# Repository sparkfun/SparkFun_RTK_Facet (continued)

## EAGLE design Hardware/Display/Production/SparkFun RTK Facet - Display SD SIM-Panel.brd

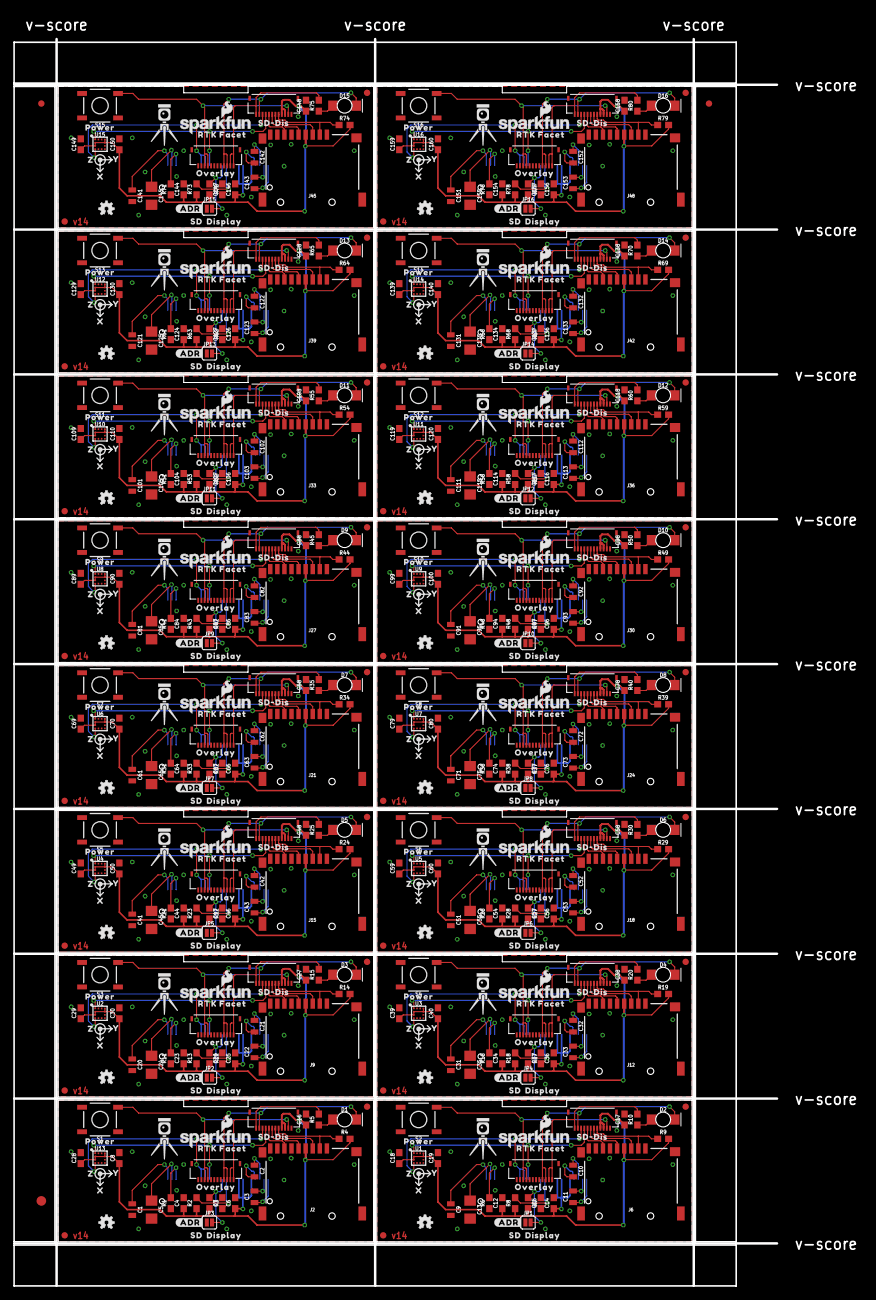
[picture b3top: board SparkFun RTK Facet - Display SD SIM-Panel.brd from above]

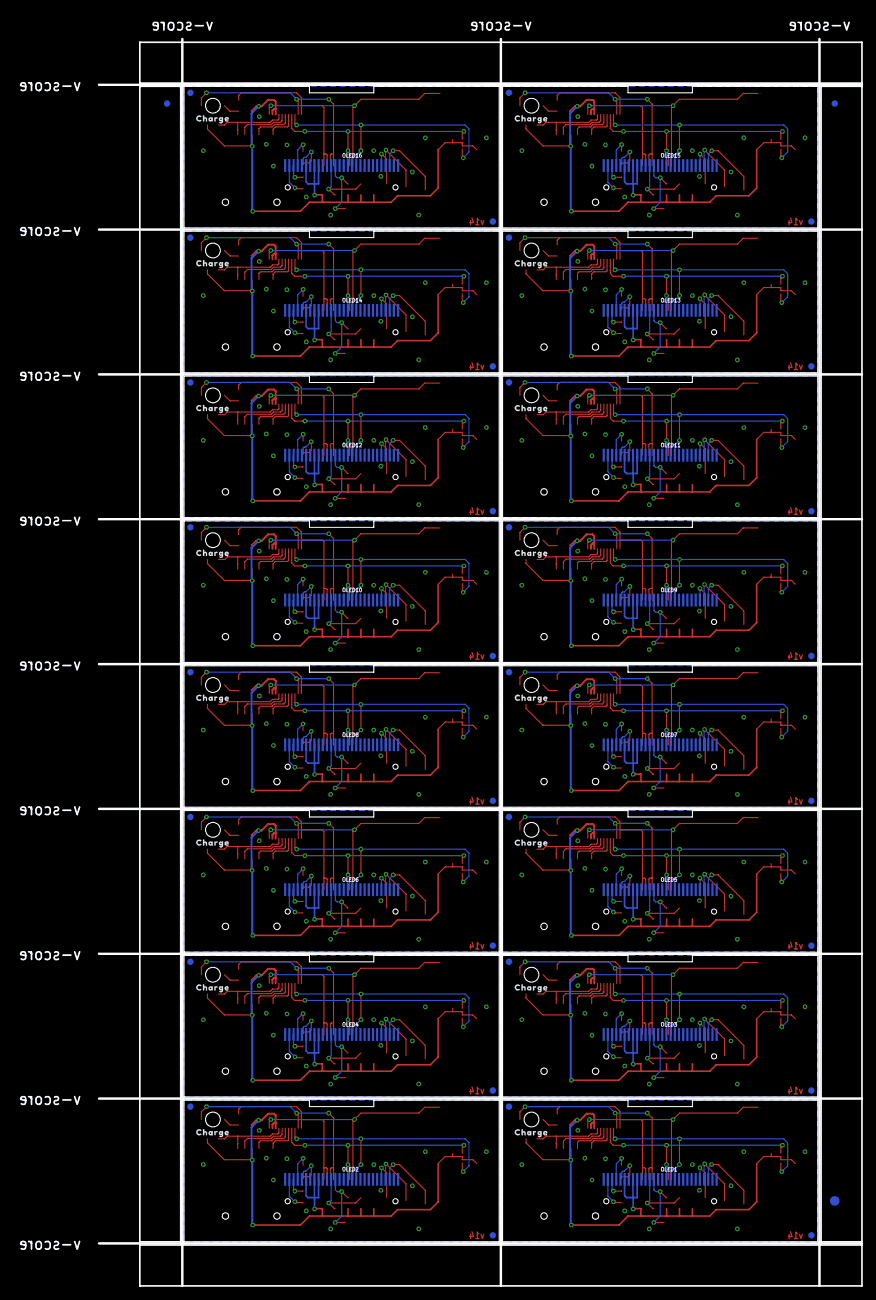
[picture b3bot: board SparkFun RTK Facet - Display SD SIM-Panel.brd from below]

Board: 2 copper layers, 118.6 x 193.8 mm, 662 parts (67 on the bottom side), 336 nets.

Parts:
C1, C9, C20, C31, C41, C51, C61, C71, C81, C91, C101, C111, C121, C131, C141, C151: 2.2uF; 0805
C2, C3, C10, C11, C21, C22, C32, C33, C42, C43, C52, C53, C62, C63, C72, C73, C82, C83, C92, C93, C102, C103, C112, C113, C122, C123, C132, C133, C142, C143, C152, C153: 1.0uF; 0805
C4, C6, C7, C12, C14, C15, C23, C25, C26, C34, C36, C37, C44, C46, C47, C54, C56, C57, C64, C66, C67, C74, C76, C77, C84, C86, C87, C94, C96, C97, C104, C106, C107, C114, C116, C117, C124, C126, C127, C134, C136, C137, C144, C146, C147, C154, C156, C157: 1.0uF; 0603
C5, C13, C24, C35, C45, C55, C65, C75, C85, C95, C105, C115, C125, C135, C145, C155: 4.7uF; 1206
C8, C19, C30, C40, C50, C60, C70, C80, C90, C100, C110, C120, C130, C140, C150, C160: 10uF; 0603
C16, C17, C18, C27, C28, C29, C38, C39, C48, C49, C58, C59, C68, C69, C78, C79, C88, C89, C98, C99, C108, C109, C118, C119, C128, C129, C138, C139, C148, C149, C158, C159: 0.1uF; 0603
D1, D2, D3, D4, D5, D6, D7, D8, D9, D10, D11, D12, D13, D14, D15, D16: Green; LED-1206-BOTTOM
E$1, E$2, E$3, E$4: FIDUCIAL-1X2
E$5, E$6: FIDUCIAL-1.5X3
FID1, FID2, FID3, FID4, FID5, FID6, FID7, FID8, FID9, FID10, FID11, FID12, FID13, FID14, FID15, FID16, FID17, FID18, FID19, FID20, FID21, FID22, FID23, FID24, FID25, FID26, FID27, FID28, FID29, FID30, FID31, FID32, FID33, FID34, FID35, FID36, FID37, FID38, FID39, FID40, FID41, FID42, FID43, FID44, FID45, FID46, FID47, FID48, FID49, FID50, FID51, FID52, FID53, FID54, FID55, FID56, FID57, FID58, FID59, FID60, FID61, FID62, FID63, FID64: FIDUCIAL1X2; FIDUCIAL-1X2
J1, J3, J4, J5, J7, J8, J10, J11, J13, J14, J16, J17, J19, J20, J22, J23, J25, J26, J28, J29, J31, J32, J34, J35, J37, J38, J40, J41, J43, J44, J46, J47: FPC_12_0.5MM_BACKFLIP; FPC_12_DOUBLESIDED_BACKFLIP
J2, J6, J9, J12, J15, J18, J21, J24, J27, J30, J33, J36, J39, J42, J45, J48: MICRO-SD-PUSH-PUSH-EXT-PIN; MICROSD-EXTERNALPIN
JP1, JP2, JP3, JP4, JP5, JP6, JP7, JP8, JP9, JP10, JP11, JP12, JP13, JP14, JP15, JP16: SMT-JUMPER_2_NO_SILK
LOGO1, LOGO3, LOGO4, LOGO7, LOGO9, LOGO11, LOGO13, LOGO15, LOGO17, LOGO19, LOGO21, LOGO23, LOGO25, LOGO27, LOGO29, LOGO31: OSHW-LOGOMINI; OSHW-LOGO-MINI
LOGO2, LOGO5, LOGO6, LOGO8, LOGO10, LOGO12, LOGO14, LOGO16, LOGO18, LOGO20, LOGO22, LOGO24, LOGO26, LOGO28, LOGO30, LOGO32: SFE_LOGO_NAME_FLAME.1_INCH; SFE_LOGO_NAME_FLAME_.1
OLED1, OLED2, OLED3, OLED4, OLED5, OLED6, OLED7, OLED8, OLED9, OLED10, OLED11, OLED12, OLED13, OLED14, OLED15, OLED16: OLED0.66; OLED-0.66-64X48
R1, R6, R11, R16, R21, R26, R31, R36, R41, R46, R51, R56, R61, R66, R71, R76: 390k; 0603
R2, R3, R7, R8, R12, R13, R17, R18, R22, R23, R27, R28, R32, R33, R37, R38, R42, R43, R47, R48, R52, R53, R57, R58, R62, R63, R67, R68, R72, R73, R77, R78: 10k; 0603
R4, R9, R14, R19, R24, R29, R34, R39, R44, R49, R54, R59, R64, R69, R74, R79: 100k; 0603
R5, R10, R15, R20, R25, R30, R35, R40, R45, R50, R55, R60, R65, R70, R75, R80: 1k; 0603
S1, S2, S3, S4, S5, S6, S7, S8, S9, S10, S11, S12, S13, S14, S15, S16: MOMENTARY-SWITCH-SPST-SMD-5.2MM-TALL; TACTILE_SWITCH_SMD_5.2MM
U1, U2, U3, U4, U5, U6, U7, U8, U9, U10, U11, U12, U13, U14, U15, U16: LIS2DH12; LGA-12-LISDH12
U$1, U$16, U$28, U$40, U$52, U$64, U$76, U$88, U$100, U$112, U$124, U$136, U$148, U$160, U$172, U$184: SD#DIS0
U$2, U$18, U$30, U$42, U$54, U$66, U$78, U$90, U$102, U$114, U$126, U$138, U$150, U$162, U$174, U$186: OVERLAY0
U$3, U$6, U$25, U$37, U$49, U$61, U$73, U$85, U$97, U$109, U$121, U$133, U$145, U$157, U$169, U$181: DISPLAY0
U$4, U$14, U$26, U$38, U$50, U$62, U$74, U$86, U$98, U$110, U$122, U$134, U$146, U$158, U$170, U$182: SD1
U$5, U$24, U$36, U$48, U$60, U$72, U$84, U$96, U$108, U$120, U$132, U$144, U$156, U$168, U$180, U$192: RTK5#SVG0
U$7, U$15, U$27, U$39, U$51, U$63, U$75, U$87, U$99, U$111, U$123, U$135, U$147, U$159, U$171, U$183: #ADR#0
U$8, U$17, U$29, U$41, U$53, U$65, U$77, U$89, U$101, U$113, U$125, U$137, U$149, U$161, U$173, U$185: CHARGE0
U$9, U$19, U$31, U$43, U$55, U$67, U$79, U$91, U$103, U$115, U$127, U$139, U$151, U$163, U$175, U$187: POWER0
U$10, U$20, U$32, U$44, U$56, U$68, U$80, U$92, U$104, U$116, U$128, U$140, U$152, U$164, U$176, U$188: X0
U$11, U$21, U$33, U$45, U$57, U$69, U$81, U$93, U$105, U$117, U$129, U$141, U$153, U$165, U$177, U$189: Y1
U$12, U$22, U$34, U$46, U$58, U$70, U$82, U$94, U$106, U$118, U$130, U$142, U$154, U$166, U$178, U$190: Z2
U$13, U$23, U$35, U$47, U$59, U$71, U$83, U$95, U$107, U$119, U$131, U$143, U$155, U$167, U$179, U$191: RTK_FACET0

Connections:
3.3V: C4.1, C6.1, C8.1, C16.1, C28.1, J1.3, J1.4, J2.4, OLED1.6, OLED1.8, OLED1.9, R2.1, R3.2, R4.2, U13.2, U13.3, U13.9, U13.10
3.3V1: C12.1, C14.1, C17.1, C18.1, C19.1, J4.3, J4.4, J6.4, OLED2.6, OLED2.8, OLED2.9, R7.2, R8.1, R9.2, U1.2, U1.3, U1.9, U1.10
3.3V2: C23.1, C25.1, C27.1, C29.1, C30.1, J7.3, J7.4, J9.4, OLED3.6, OLED3.8, OLED3.9, R12.2, R13.1, R14.2, U2.2, U2.3, U2.9, U2.10
3.3V3: C34.1, C36.1, C38.1, C39.1, C40.1, J10.3, J10.4, J12.4, OLED4.6, OLED4.8, OLED4.9, R17.2, R18.1, R19.2, U3.2, U3.3, U3.9, U3.10
3.3V4: C44.1, C46.1, C48.1, C49.1, C50.1, J13.3, J13.4, J15.4, OLED5.6, OLED5.8, OLED5.9, R22.2, R23.1, R24.2, U4.2, U4.3, U4.9, U4.10
3.3V5: C54.1, C56.1, C58.1, C59.1, C60.1, J16.3, J16.4, J18.4, OLED6.6, OLED6.8, OLED6.9, R27.2, R28.1, R29.2, U5.2, U5.3, U5.9, U5.10
3.3V6: C64.1, C66.1, C68.1, C69.1, C70.1, J19.3, J19.4, J21.4, OLED7.6, OLED7.8, OLED7.9, R32.2, R33.1, R34.2, U6.2, U6.3, U6.9, U6.10
3.3V7: C74.1, C76.1, C78.1, C79.1, C80.1, J22.3, J22.4, J24.4, OLED8.6, OLED8.8, OLED8.9, R37.2, R38.1, R39.2, U7.2, U7.3, U7.9, U7.10
3.3V8: C84.1, C86.1, C88.1, C89.1, C90.1, J25.3, J25.4, J27.4, OLED9.6, OLED9.8, OLED9.9, R42.2, R43.1, R44.2, U8.2, U8.3, U8.9, U8.10
3.3V9: C94.1, C96.1, C98.1, C99.1, C100.1, J28.3, J28.4, J30.4, OLED10.6, OLED10.8, OLED10.9, R47.2, R48.1, R49.2, U9.2, U9.3, U9.9, U9.10
3.3V10: C104.1, C106.1, C108.1, C109.1, C110.1, J31.3, J31.4, J33.4, OLED11.6, OLED11.8, OLED11.9, R52.2, R53.1, R54.2, U10.2, U10.3, U10.9, U10.10
3.3V11: C114.1, C116.1, C118.1, C119.1, C120.1, J34.3, J34.4, J36.4, OLED12.6, OLED12.8, OLED12.9, R57.2, R58.1, R59.2, U11.2, U11.3, U11.9, U11.10
3.3V12: C124.1, C126.1, C128.1, C129.1, C130.1, J37.3, J37.4, J39.4, OLED13.6, OLED13.8, OLED13.9, R62.2, R63.1, R64.2, U12.2, U12.3, U12.9, U12.10
3.3V13: C134.1, C136.1, C138.1, C139.1, C140.1, J40.3, J40.4, J42.4, OLED14.6, OLED14.8, OLED14.9, R67.2, R68.1, R69.2, U14.2, U14.3, U14.9, U14.10
3.3V14: C144.1, C146.1, C148.1, C149.1, C150.1, J43.3, J43.4, J45.4, OLED15.6, OLED15.8, OLED15.9, R72.2, R73.1, R74.2, U15.2, U15.3, U15.9, U15.10
3.3V15: C154.1, C156.1, C158.1, C159.1, C160.1, J46.3, J46.4, J48.4, OLED16.6, OLED16.8, OLED16.9, R77.2, R78.1, R79.2, U16.2, U16.3, U16.9, U16.10
C1P: C2.1, OLED1.4
C1P1: C10.1, OLED2.4
C1P2: C21.1, OLED3.4
C1P3: C32.1, OLED4.4
C1P4: C42.1, OLED5.4
C1P5: C52.1, OLED6.4
C1P6: C62.1, OLED7.4
C1P7: C72.1, OLED8.4
C1P8: C82.1, OLED9.4
C1P9: C92.1, OLED10.4
C1P10: C102.1, OLED11.4
C1P11: C112.1, OLED12.4
C1P12: C122.1, OLED13.4
C1P13: C132.1, OLED14.4
C1P14: C142.1, OLED15.4
C1P15: C152.1, OLED16.4
C2N: C3.2, OLED1.3
C2N1: C11.2, OLED2.3
C2N2: C22.2, OLED3.3
C2N3: C33.2, OLED4.3
C2N4: C43.2, OLED5.3
C2N5: C53.2, OLED6.3
C2N6: C63.2, OLED7.3
C2N7: C73.2, OLED8.3
C2N8: C83.2, OLED9.3
C2N9: C93.2, OLED10.3
C2N10: C103.2, OLED11.3
C2N11: C113.2, OLED12.3
C2N12: C123.2, OLED13.3
C2N13: C133.2, OLED14.3
C2N14: C143.2, OLED15.3
C2N15: C153.2, OLED16.3
CHARGE_LED: D1.C, J1.11, J3.3, J3.4
CHARGE_LED1: D2.C, J4.11, J5.3, J5.4
CHARGE_LED2: D3.C, J7.11, J8.3, J8.4
CHARGE_LED3: D4.C, J10.11, J11.3, J11.4
CHARGE_LED4: D5.C, J13.11, J14.3, J14.4
CHARGE_LED5: D6.C, J16.11, J17.3, J17.4
CHARGE_LED6: D7.C, J19.11, J20.3, J20.4
CHARGE_LED7: D8.C, J22.11, J23.3, J23.4
CHARGE_LED8: D9.C, J25.11, J26.3, J26.4
CHARGE_LED9: D10.C, J28.11, J29.3, J29.4
CHARGE_LED10: D11.C, J31.11, J32.3, J32.4
CHARGE_LED11: D12.C, J34.11, J35.3, J35.4
CHARGE_LED12: D13.C, J37.11, J38.3, J38.4
CHARGE_LED13: D14.C, J40.11, J41.3, J41.4
CHARGE_LED14: D15.C, J43.11, J44.3, J44.4
CHARGE_LED15: D16.C, J46.11, J47.3, J47.4
D/C: JP3.2, OLED1.13, R3.1
D/C1: JP1.2, OLED2.13, R7.1
D/C2: JP2.2, OLED3.13, R12.1
D/C3: JP4.2, OLED4.13, R17.1
D/C4: JP5.2, OLED5.13, R22.1
D/C5: JP6.2, OLED6.13, R27.1
D/C6: JP7.2, OLED7.13, R32.1
D/C7: JP8.2, OLED8.13, R37.1
D/C8: JP9.2, OLED9.13, R42.1
D/C9: JP10.2, OLED10.13, R47.1
D/C10: JP11.2, OLED11.13, R52.1
D/C11: JP12.2, OLED12.13, R57.1
D/C12: JP13.2, OLED13.13, R62.1
D/C13: JP14.2, OLED14.13, R67.1
D/C14: JP15.2, OLED15.13, R72.1
D/C15: JP16.2, OLED16.13, R77.1
ESP_21/SDA: J1.10, OLED1.17, OLED1.18, U13.4
ESP_21/SDA1: J4.10, OLED2.17, OLED2.18, U1.4
ESP_21/SDA2: J7.10, OLED3.17, OLED3.18, U2.4
ESP_21/SDA3: J10.10, OLED4.17, OLED4.18, U3.4
ESP_21/SDA4: J13.10, OLED5.17, OLED5.18, U4.4
ESP_21/SDA5: J16.10, OLED6.17, OLED6.18, U5.4
ESP_21/SDA6: J19.10, OLED7.17, OLED7.18, U6.4
ESP_21/SDA7: J22.10, OLED8.17, OLED8.18, U7.4
ESP_21/SDA8: J25.10, OLED9.17, OLED9.18, U8.4
ESP_21/SDA9: J28.10, OLED10.17, OLED10.18, U9.4
ESP_21/SDA10: J31.10, OLED11.17, OLED11.18, U10.4
ESP_21/SDA11: J34.10, OLED12.17, OLED12.18, U11.4
ESP_21/SDA12: J37.10, OLED13.17, OLED13.18, U12.4
ESP_21/SDA13: J40.10, OLED14.17, OLED14.18, U14.4
ESP_21/SDA14: J43.10, OLED15.17, OLED15.18, U15.4
ESP_21/SDA15: J46.10, OLED16.17, OLED16.18, U16.4
ESP_22/SCL: J1.9, OLED1.16, U13.1
ESP_22/SCL1: J4.9, OLED2.16, U1.1
ESP_22/SCL2: J7.9, OLED3.16, U2.1
ESP_22/SCL3: J10.9, OLED4.16, U3.1
ESP_22/SCL4: J13.9, OLED5.16, U4.1
ESP_22/SCL5: J16.9, OLED6.16, U5.1
ESP_22/SCL6: J19.9, OLED7.16, U6.1
ESP_22/SCL7: J22.9, OLED8.16, U7.1
ESP_22/SCL8: J25.9, OLED9.16, U8.1
ESP_22/SCL9: J28.9, OLED10.16, U9.1
ESP_22/SCL10: J31.9, OLED11.16, U10.1
ESP_22/SCL11: J34.9, OLED12.16, U11.1
ESP_22/SCL12: J37.9, OLED13.16, U12.1
ESP_22/SCL13: J40.9, OLED14.16, U14.1
ESP_22/SCL14: J43.9, OLED15.16, U15.1
ESP_22/SCL15: J46.9, OLED16.16, U16.1
GND: C1.2, C4.2, C5.2, C6.2, C7.2, C8.2, C16.2, C28.2, J1.1, J2.6, J2.9, J2.10, J2.11, J2.12, J2.13, J3.11, J3.12, JP3.1, OLED1.1, OLED1.7, OLED1.10, OLED1.27, OLED1.28, R1.1, S1.1, U13.5, U13.6, U13.7, U13.8
GND1: C9.2, C12.2, C13.2, C14.2, C15.2, C17.2, C18.2, C19.2, J4.1, J5.11, J5.12, J6.6, J6.9, J6.10, J6.11, J6.12, J6.13, JP1.1, OLED2.1, OLED2.7, OLED2.10, OLED2.27, OLED2.28, R6.1, S2.1, U1.5, U1.6, U1.7, U1.8
GND2: C20.2, C23.2, C24.2, C25.2, C26.2, C27.2, C29.2, C30.2, J7.1, J8.11, J8.12, J9.6, J9.9, J9.10, J9.11, J9.12, J9.13, JP2.1, OLED3.1, OLED3.7, OLED3.10, OLED3.27, OLED3.28, R11.1, S3.1, U2.5, U2.6, U2.7, U2.8
GND3: C31.2, C34.2, C35.2, C36.2, C37.2, C38.2, C39.2, C40.2, J10.1, J11.11, J11.12, J12.6, J12.9, J12.10, J12.11, J12.12, J12.13, JP4.1, OLED4.1, OLED4.7, OLED4.10, OLED4.27, OLED4.28, R16.1, S4.1, U3.5, U3.6, U3.7, U3.8
GND4: C41.2, C44.2, C45.2, C46.2, C47.2, C48.2, C49.2, C50.2, J13.1, J14.11, J14.12, J15.6, J15.9, J15.10, J15.11, J15.12, J15.13, JP5.1, OLED5.1, OLED5.7, OLED5.10, OLED5.27, OLED5.28, R21.1, S5.1, U4.5, U4.6, U4.7, U4.8
GND5: C51.2, C54.2, C55.2, C56.2, C57.2, C58.2, C59.2, C60.2, J16.1, J17.11, J17.12, J18.6, J18.9, J18.10, J18.11, J18.12, J18.13, JP6.1, OLED6.1, OLED6.7, OLED6.10, OLED6.27, OLED6.28, R26.1, S6.1, U5.5, U5.6, U5.7, U5.8
GND6: C61.2, C64.2, C65.2, C66.2, C67.2, C68.2, C69.2, C70.2, J19.1, J20.11, J20.12, J21.6, J21.9, J21.10, J21.11, J21.12, J21.13, JP7.1, OLED7.1, OLED7.7, OLED7.10, OLED7.27, OLED7.28, R31.1, S7.1, U6.5, U6.6, U6.7, U6.8
GND7: C71.2, C74.2, C75.2, C76.2, C77.2, C78.2, C79.2, C80.2, J22.1, J23.11, J23.12, J24.6, J24.9, J24.10, J24.11, J24.12, J24.13, JP8.1, OLED8.1, OLED8.7, OLED8.10, OLED8.27, OLED8.28, R36.1, S8.1, U7.5, U7.6, U7.7, U7.8
GND8: C81.2, C84.2, C85.2, C86.2, C87.2, C88.2, C89.2, C90.2, J25.1, J26.11, J26.12, J27.6, J27.9, J27.10, J27.11, J27.12, J27.13, JP9.1, OLED9.1, OLED9.7, OLED9.10, OLED9.27, OLED9.28, R41.1, S9.1, U8.5, U8.6, U8.7, U8.8
GND9: C91.2, C94.2, C95.2, C96.2, C97.2, C98.2, C99.2, C100.2, J28.1, J29.11, J29.12, J30.6, J30.9, J30.10, J30.11, J30.12, J30.13, JP10.1, OLED10.1, OLED10.7, OLED10.10, OLED10.27, OLED10.28, R46.1, S10.1, U9.5, U9.6, U9.7, U9.8
GND10: C101.2, C104.2, C105.2, C106.2, C107.2, C108.2, C109.2, C110.2, J31.1, J32.11, J32.12, J33.6, J33.9, J33.10, J33.11, J33.12, J33.13, JP11.1, OLED11.1, OLED11.7, OLED11.10, OLED11.27, OLED11.28, R51.1, S11.1, U10.5, U10.6, U10.7, U10.8
GND11: C111.2, C114.2, C115.2, C116.2, C117.2, C118.2, C119.2, C120.2, J34.1, J35.11, J35.12, J36.6, J36.9, J36.10, J36.11, J36.12, J36.13, JP12.1, OLED12.1, OLED12.7, OLED12.10, OLED12.27, OLED12.28, R56.1, S12.1, U11.5, U11.6, U11.7, U11.8
GND12: C121.2, C124.2, C125.2, C126.2, C127.2, C128.2, C129.2, C130.2, J37.1, J38.11, J38.12, J39.6, J39.9, J39.10, J39.11, J39.12, J39.13, JP13.1, OLED13.1, OLED13.7, OLED13.10, OLED13.27, OLED13.28, R61.1, S13.1, U12.5, U12.6, U12.7, U12.8
GND13: C131.2, C134.2, C135.2, C136.2, C137.2, C138.2, C139.2, C140.2, J40.1, J41.11, J41.12, J42.6, J42.9, J42.10, J42.11, J42.12, J42.13, JP14.1, OLED14.1, OLED14.7, OLED14.10, OLED14.27, OLED14.28, R66.1, S14.1, U14.5, U14.6, U14.7, U14.8
GND14: C141.2, C144.2, C145.2, C146.2, C147.2, C148.2, C149.2, C150.2, J43.1, J44.11, J44.12, J45.6, J45.9, J45.10, J45.11, J45.12, J45.13, JP15.1, OLED15.1, OLED15.7, OLED15.10, OLED15.27, OLED15.28, R71.1, S15.1, U15.5, U15.6, U15.7, U15.8
GND15: C151.2, C154.2, C155.2, C156.2, C157.2, C158.2, C159.2, C160.2, J46.1, J47.11, J47.12, J48.6, J48.9, J48.10, J48.11, J48.12, J48.13, JP16.1, OLED16.1, OLED16.7, OLED16.10, OLED16.27, OLED16.28, R76.1, S16.1, U16.5, U16.6, U16.7, U16.8
IREF: OLED1.24, R1.2
IREF1: OLED2.24, R6.2
IREF2: OLED3.24, R11.2
IREF3: OLED4.24, R16.2
IREF4: OLED5.24, R21.2
IREF5: OLED6.24, R26.2
IREF6: OLED7.24, R31.2
IREF7: OLED8.24, R36.2
IREF8: OLED9.24, R41.2
IREF9: OLED10.24, R46.2
IREF10: OLED11.24, R51.2
IREF11: OLED12.24, R56.2
IREF12: OLED13.24, R61.2
IREF13: OLED14.24, R66.2
IREF14: OLED15.24, R71.2
IREF15: OLED16.24, R76.2
unnamed: C3.1, OLED1.2
unnamed: C2.2, OLED1.5
unnamed: D1.A, R5.1
unnamed: C11.1, OLED2.2
unnamed: C10.2, OLED2.5
unnamed: D2.A, R10.1
unnamed: C22.1, OLED3.2
unnamed: C21.2, OLED3.5
unnamed: D3.A, R15.1
unnamed: C33.1, OLED4.2
unnamed: C32.2, OLED4.5
unnamed: D4.A, R20.1
unnamed: C43.1, OLED5.2
unnamed: C42.2, OLED5.5
unnamed: D5.A, R25.1
unnamed: C53.1, OLED6.2
unnamed: C52.2, OLED6.5
unnamed: D6.A, R30.1
unnamed: C63.1, OLED7.2
unnamed: C62.2, OLED7.5
unnamed: D7.A, R35.1
unnamed: C73.1, OLED8.2
unnamed: C72.2, OLED8.5
unnamed: D8.A, R40.1
unnamed: C83.1, OLED9.2
unnamed: C82.2, OLED9.5
unnamed: D9.A, R45.1
unnamed: C93.1, OLED10.2
unnamed: C92.2, OLED10.5
unnamed: D10.A, R50.1
unnamed: C103.1, OLED11.2
unnamed: C102.2, OLED11.5
unnamed: D11.A, R55.1
unnamed: C113.1, OLED12.2
unnamed: C112.2, OLED12.5
unnamed: D12.A, R60.1
unnamed: C123.1, OLED13.2
unnamed: C122.2, OLED13.5
unnamed: D13.A, R65.1
unnamed: C133.1, OLED14.2
unnamed: C132.2, OLED14.5
unnamed: D14.A, R70.1
unnamed: C143.1, OLED15.2
unnamed: C142.2, OLED15.5
unnamed: D15.A, R75.1
unnamed: C153.1, OLED16.2
unnamed: C152.2, OLED16.5
unnamed: D16.A, R80.1
POWER_BTN: J1.2, J3.9, J3.10, S1.3
POWER_BTN1: J4.2, J5.9, J5.10, S2.3
POWER_BTN2: J7.2, J8.9, J8.10, S3.3
POWER_BTN3: J10.2, J11.9, J11.10, S4.3
POWER_BTN4: J13.2, J14.9, J14.10, S5.3
POWER_BTN5: J16.2, J17.9, J17.10, S6.3
POWER_BTN6: J19.2, J20.9, J20.10, S7.3
POWER_BTN7: J22.2, J23.9, J23.10, S8.3
POWER_BTN8: J25.2, J26.9, J26.10, S9.3
POWER_BTN9: J28.2, J29.9, J29.10, S10.3
POWER_BTN10: J31.2, J32.9, J32.10, S11.3
POWER_BTN11: J34.2, J35.9, J35.10, S12.3
POWER_BTN12: J37.2, J38.9, J38.10, S13.3
POWER_BTN13: J40.2, J41.9, J41.10, S14.3
POWER_BTN14: J43.2, J44.9, J44.10, S15.3
POWER_BTN15: J46.2, J47.9, J47.10, S16.3
RESET: C7.1, OLED1.12, R2.2
RESET1: C15.1, OLED2.12, R8.2
RESET2: C26.1, OLED3.12, R13.2
RESET3: C37.1, OLED4.12, R18.2
RESET4: C47.1, OLED5.12, R23.2
RESET5: C57.1, OLED6.12, R28.2
RESET6: C67.1, OLED7.12, R33.2
RESET7: C77.1, OLED8.12, R38.2
RESET8: C87.1, OLED9.12, R43.2
RESET9: C97.1, OLED10.12, R48.2
RESET10: C107.1, OLED11.12, R53.2
RESET11: C117.1, OLED12.12, R58.2
RESET12: C127.1, OLED13.12, R63.2
RESET13: C137.1, OLED14.12, R68.2
RESET14: C147.1, OLED15.12, R73.2
RESET15: C157.1, OLED16.12, R78.2
SD_!CS!: J1.5, J2.2, R4.1
SD_!CS!1: J4.5, J6.2, R9.1
SD_!CS!2: J7.5, J9.2, R14.1
SD_!CS!3: J10.5, J12.2, R19.1
SD_!CS!4: J13.5, J15.2, R24.1
SD_!CS!5: J16.5, J18.2, R29.1
SD_!CS!6: J19.5, J21.2, R34.1
SD_!CS!7: J22.5, J24.2, R39.1
SD_!CS!8: J25.5, J27.2, R44.1
SD_!CS!9: J28.5, J30.2, R49.1
SD_!CS!10: J31.5, J33.2, R54.1
SD_!CS!11: J34.5, J36.2, R59.1
SD_!CS!12: J37.5, J39.2, R64.1
SD_!CS!13: J40.5, J42.2, R69.1
SD_!CS!14: J43.5, J45.2, R74.1
SD_!CS!15: J46.5, J48.2, R79.1
SD_CIPO: J1.8, J2.7
SD_CIPO1: J4.8, J6.7
SD_CIPO2: J7.8, J9.7
SD_CIPO3: J10.8, J12.7
SD_CIPO4: J13.8, J15.7
SD_CIPO5: J16.8, J18.7
SD_CIPO6: J19.8, J21.7
SD_CIPO7: J22.8, J24.7
SD_CIPO8: J25.8, J27.7
SD_CIPO9: J28.8, J30.7
SD_CIPO10: J31.8, J33.7
SD_CIPO11: J34.8, J36.7
SD_CIPO12: J37.8, J39.7
SD_CIPO13: J40.8, J42.7
SD_CIPO14: J43.8, J45.7
SD_CIPO15: J46.8, J48.7
SD_COPI: J1.6, J2.3
SD_COPI1: J4.6, J6.3
SD_COPI2: J7.6, J9.3
SD_COPI3: J10.6, J12.3
SD_COPI4: J13.6, J15.3
SD_COPI5: J16.6, J18.3
SD_COPI6: J19.6, J21.3
SD_COPI7: J22.6, J24.3
SD_COPI8: J25.6, J27.3
SD_COPI9: J28.6, J30.3
SD_COPI10: J31.6, J33.3
SD_COPI11: J34.6, J36.3
SD_COPI12: J37.6, J39.3
SD_COPI13: J40.6, J42.3
SD_COPI14: J43.6, J45.3
SD_COPI15: J46.6, J48.3
SD_SCK: J1.7, J2.5
SD_SCK1: J4.7, J6.5
SD_SCK2: J7.7, J9.5
SD_SCK3: J10.7, J12.5
SD_SCK4: J13.7, J15.5
SD_SCK5: J16.7, J18.5
SD_SCK6: J19.7, J21.5
SD_SCK7: J22.7, J24.5
SD_SCK8: J25.7, J27.5
SD_SCK9: J28.7, J30.5
SD_SCK10: J31.7, J33.5
SD_SCK11: J34.7, J36.5
SD_SCK12: J37.7, J39.5
SD_SCK13: J40.7, J42.5
SD_SCK14: J43.7, J45.5
SD_SCK15: J46.7, J48.5
VCC: C1.1, OLED1.26
VCC1: C9.1, OLED2.26
VCC2: C20.1, OLED3.26
VCC3: C31.1, OLED4.26
VCC4: C41.1, OLED5.26
VCC5: C51.1, OLED6.26
VCC6: C61.1, OLED7.26
VCC7: C71.1, OLED8.26
VCC8: C81.1, OLED9.26
VCC9: C91.1, OLED10.26
VCC10: C101.1, OLED11.26
VCC11: C111.1, OLED12.26
VCC12: C121.1, OLED13.26
VCC13: C131.1, OLED14.26
VCC14: C141.1, OLED15.26
VCC15: C151.1, OLED16.26
VCOMH: C5.1, OLED1.25
VCOMH1: C13.1, OLED2.25
VCOMH2: C24.1, OLED3.25
VCOMH3: C35.1, OLED4.25
VCOMH4: C45.1, OLED5.25
VCOMH5: C55.1, OLED6.25
VCOMH6: C65.1, OLED7.25
VCOMH7: C75.1, OLED8.25
VCOMH8: C85.1, OLED9.25
VCOMH9: C95.1, OLED10.25
VCOMH10: C105.1, OLED11.25
VCOMH11: C115.1, OLED12.25
VCOMH12: C125.1, OLED13.25
VCOMH13: C135.1, OLED14.25
VCOMH14: C145.1, OLED15.25
VCOMH15: C155.1, OLED16.25
V_USB: J1.12, J3.1, J3.2, R5.2
V_USB1: J4.12, J5.1, J5.2, R10.2
V_USB2: J7.12, J8.1, J8.2, R15.2
V_USB3: J10.12, J11.1, J11.2, R20.2
V_USB4: J13.12, J14.1, J14.2, R25.2
V_USB5: J16.12, J17.1, J17.2, R30.2
V_USB6: J19.12, J20.1, J20.2, R35.2
V_USB7: J22.12, J23.1, J23.2, R40.2
V_USB8: J25.12, J26.1, J26.2, R45.2
V_USB9: J28.12, J29.1, J29.2, R50.2
V_USB10: J31.12, J32.1, J32.2, R55.2
V_USB11: J34.12, J35.1, J35.2, R60.2
V_USB12: J37.12, J38.1, J38.2, R65.2
V_USB13: J40.12, J41.1, J41.2, R70.2
V_USB14: J43.12, J44.1, J44.2, R75.2
V_USB15: J46.12, J47.1, J47.2, R80.2

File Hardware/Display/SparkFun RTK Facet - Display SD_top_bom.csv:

Comment,Designator,Footprint,LCSC Part #
OLED0.66-TRIMTRIM,OLED1,OLED-0.66-64X48-TRIM,C88334 
0.1uF,C16 C28,603,C1590 
1.0uF,C2 C3,805,C15849 
1.0uF,C4 C6 C7,603,C1592 
1k,R5,603,C22548 
2.2uF,C1,805,C19110 
4.7uF,C5,1206,C51205 
10k,R2 R3,603,C98220 
10uF,C8,603,C19702 
100k,R4,603,C14675 
390k,R1,603,C863775 
FPC_12_0.5MM_BACKFLIP,J1,FPC_12_DOUBLESIDED_BACKFLIP,C5213751 
Green,D1,LED-1206-BOTTOM,C125106 
MICRO-SD-PUSH-PUSH-EXT-PIN,J2,MICROSD-EXTERNALPIN,C720505 
MOMENTARY-SWITCH-SPST-SMD-5.2MM-TALL,S1,TACTILE_SWITCH_SMD_5.2MM,C318887 
6P_1MM-LIF Connector,JP1,6P_1MM-LIF Connector,C2915488
